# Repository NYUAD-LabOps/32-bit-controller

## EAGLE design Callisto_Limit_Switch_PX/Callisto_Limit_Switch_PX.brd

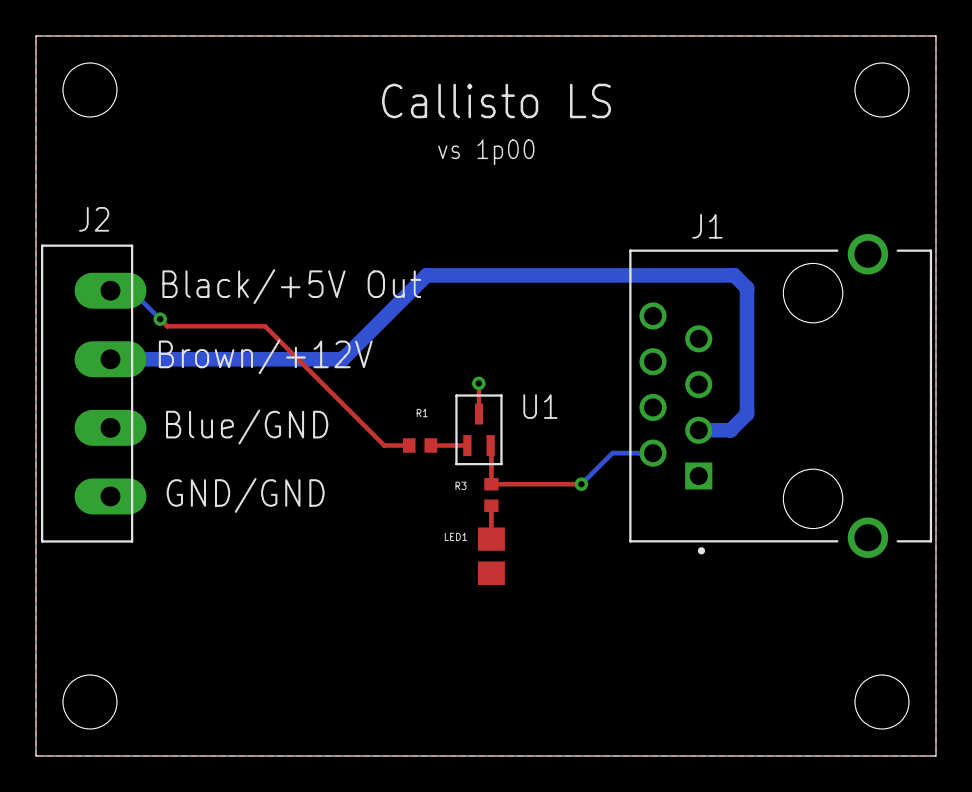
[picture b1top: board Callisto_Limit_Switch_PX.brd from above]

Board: 2 copper layers, 50.0 x 40.0 mm, 6 parts (0 on the bottom side), 6 nets.

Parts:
J1: RJ45_TH_VERT; ASSMANN_A-2014-2S-4-N-R
J2: 4-pos; 1X4_3.81MM_PITCH
LED1: Green; 0805
R1: 2.2K; 0402
R3: 470R0; 0402
U1: NPN; SOT323

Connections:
1_LS: J1.2, R3.P$2, U1.2
BLACK: J2.P$1, R1.P$1
GND: J1.1, J1.6, J2.P$3, J2.P$4, LED1.2
unnamed: R1.P$2, U1.1
unnamed: LED1.1, R3.P$1
VDD12: J1.3, J2.P$2

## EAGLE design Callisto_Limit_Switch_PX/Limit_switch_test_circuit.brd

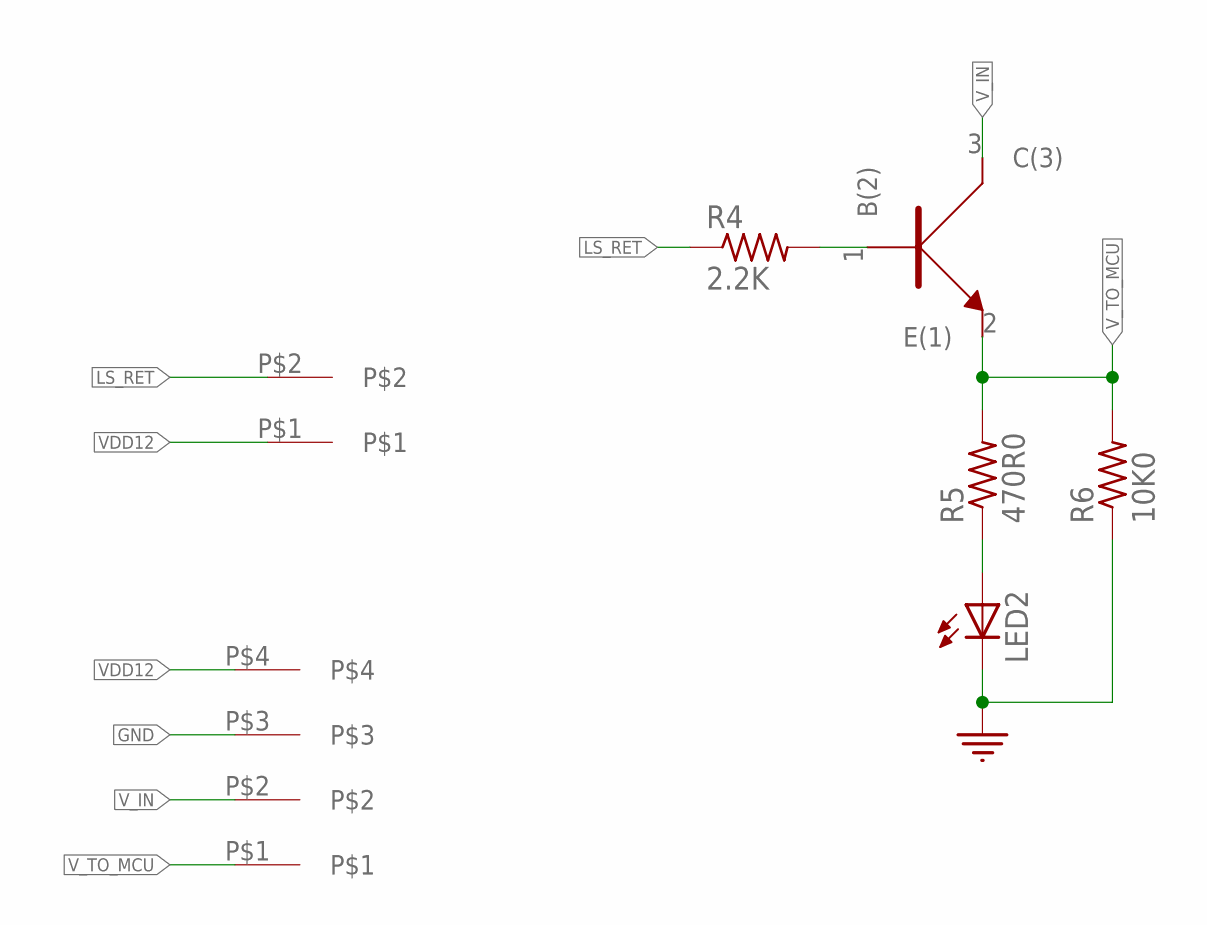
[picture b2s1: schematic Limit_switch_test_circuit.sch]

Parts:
J1: 2-pos; 2_3.81MM_PITCH
J2: 4-pos; 1X4_3.81MM_PITCH
LED2: Green; 0805
R4: 2.2K; 0402
R5: 470R0; 0402
R6: 10K0; 0402
U2: NPN; SOT323

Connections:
GND: J2.P$3, LED2.2 (C), R6.P$1 (1)
LS_RET: J1.P$2, R4.P$1 (1)
unnamed: R4.P$2 (2), U2.1 (B(2))
unnamed: LED2.1 (A), R5.P$1 (1)
VDD12: J1.P$1, J2.P$4
V_IN: J2.P$2, U2.3 (C(3))
V_TO_MCU: J2.P$1, R5.P$2 (2), R6.P$2 (2), U2.2 (E(1))

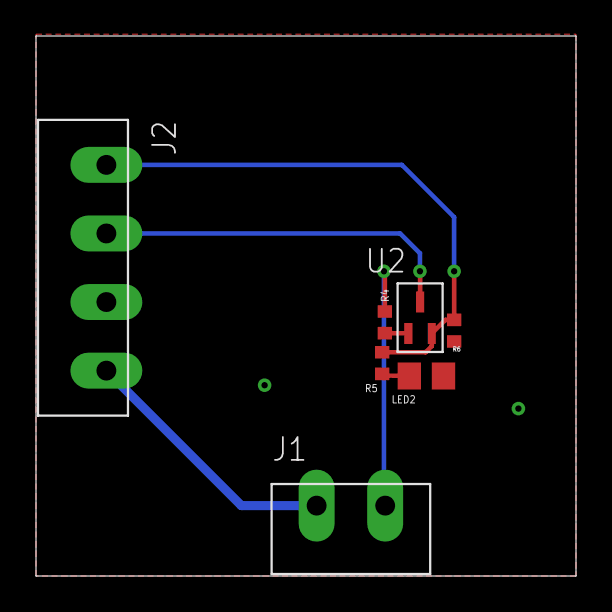
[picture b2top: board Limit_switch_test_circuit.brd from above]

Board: 2 copper layers, 30.0 x 30.0 mm, 7 parts (0 on the bottom side), 7 nets.

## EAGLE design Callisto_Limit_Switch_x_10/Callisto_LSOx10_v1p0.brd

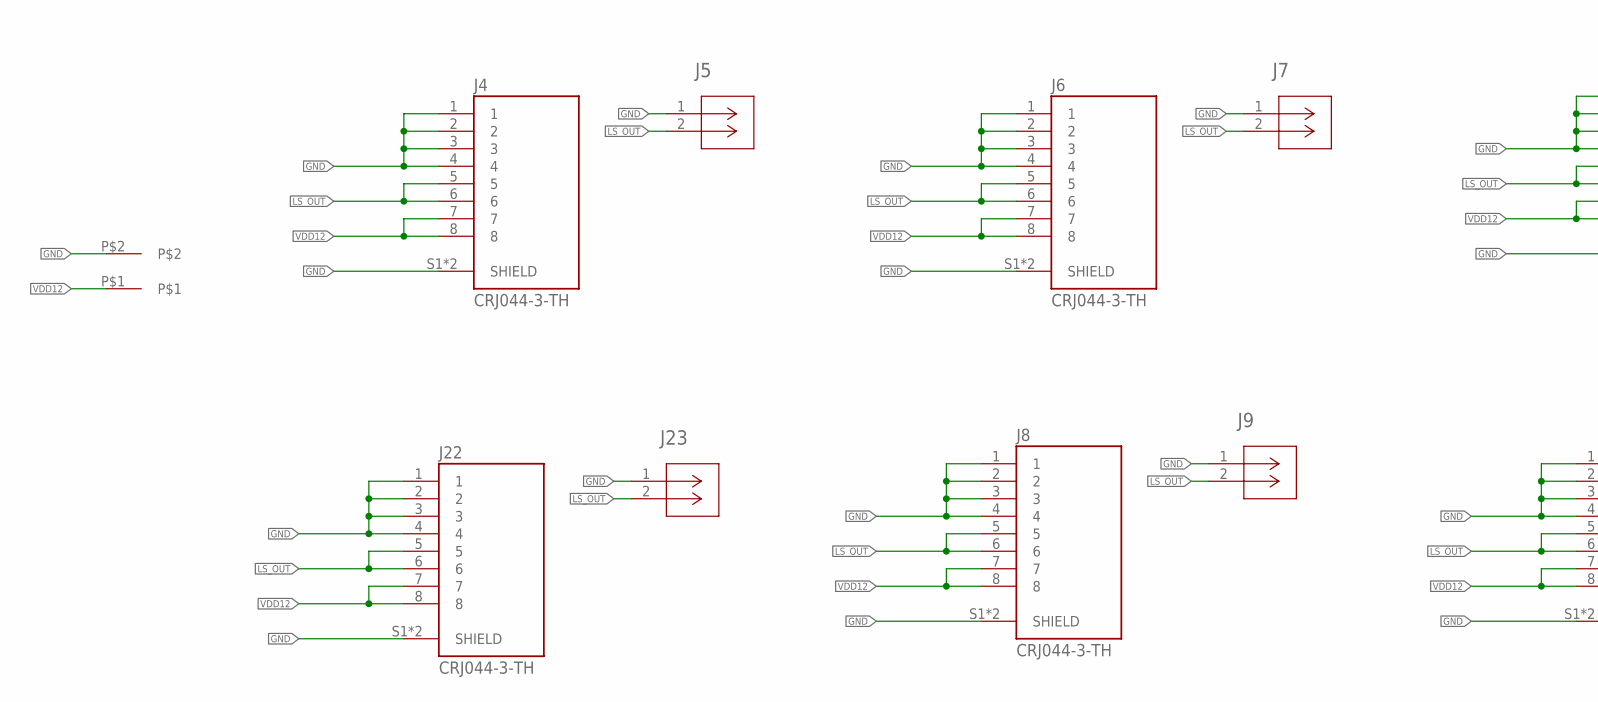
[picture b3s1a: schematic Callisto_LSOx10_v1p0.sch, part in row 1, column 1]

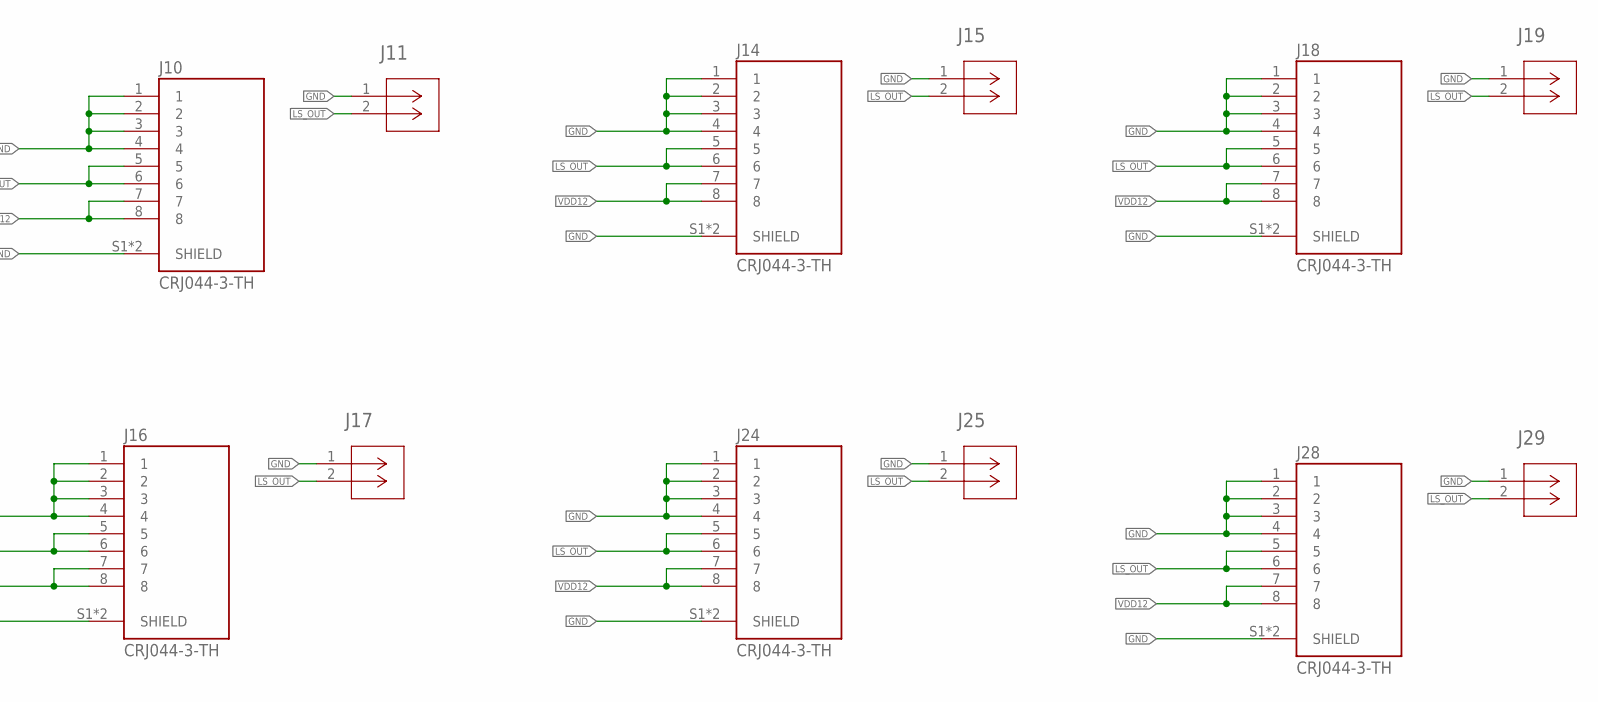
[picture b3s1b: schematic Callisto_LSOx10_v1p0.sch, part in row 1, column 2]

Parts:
J1: 2-pos; 2_3.81MM_PITCH
J4, J6, J8, J10, J14, J16, J18, J22, J24, J28: CRJ044-3-TH; CUI_CRJ044-3-TH
J5, J7, J9, J11, J15, J17, J19, J23, J25, J29: CONN_530470210_PICOBLADE_X_2; CON_530470210_MOL

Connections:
GND: J1.P$2, J4.1, J4.2, J4.3, J4.4, J4.S1 (SHIELD), J4.S2 (SHIELD), J5.1, J6.1, J6.2, J6.3, J6.4, J6.S1 (SHIELD), J6.S2 (SHIELD), J7.1, J8.1, J8.2, J8.3, J8.4, J8.S1 (SHIELD), J8.S2 (SHIELD), J9.1, J10.1, J10.2, J10.3, J10.4, J10.S1 (SHIELD), J10.S2 (SHIELD), J11.1, J14.1, J14.2, J14.3, J14.4, J14.S1 (SHIELD), J14.S2 (SHIELD), J15.1, J16.1, J16.2, J16.3, J16.4, J16.S1 (SHIELD), J16.S2 (SHIELD), J17.1, J18.1, J18.2, J18.3, J18.4, J18.S1 (SHIELD), J18.S2 (SHIELD), J19.1, J22.1, J22.2, J22.3, J22.4, J22.S1 (SHIELD), J22.S2 (SHIELD), J23.1, J24.1, J24.2, J24.3, J24.4, J24.S1 (SHIELD), J24.S2 (SHIELD), J25.1, J28.1, J28.2, J28.3, J28.4, J28.S1 (SHIELD), J28.S2 (SHIELD), J29.1
LS_OUT: J4.5, J4.6, J5.2, J6.5, J6.6, J7.2, J8.5, J8.6, J9.2, J10.5, J10.6, J11.2, J14.5, J14.6, J15.2, J16.5, J16.6, J17.2, J18.5, J18.6, J19.2, J22.5, J22.6, J23.2, J24.5, J24.6, J25.2, J28.5, J28.6, J29.2
VDD12: J1.P$1, J4.7, J4.8, J6.7, J6.8, J8.7, J8.8, J10.7, J10.8, J14.7, J14.8, J16.7, J16.8, J18.7, J18.8, J22.7, J22.8, J24.7, J24.8, J28.7, J28.8

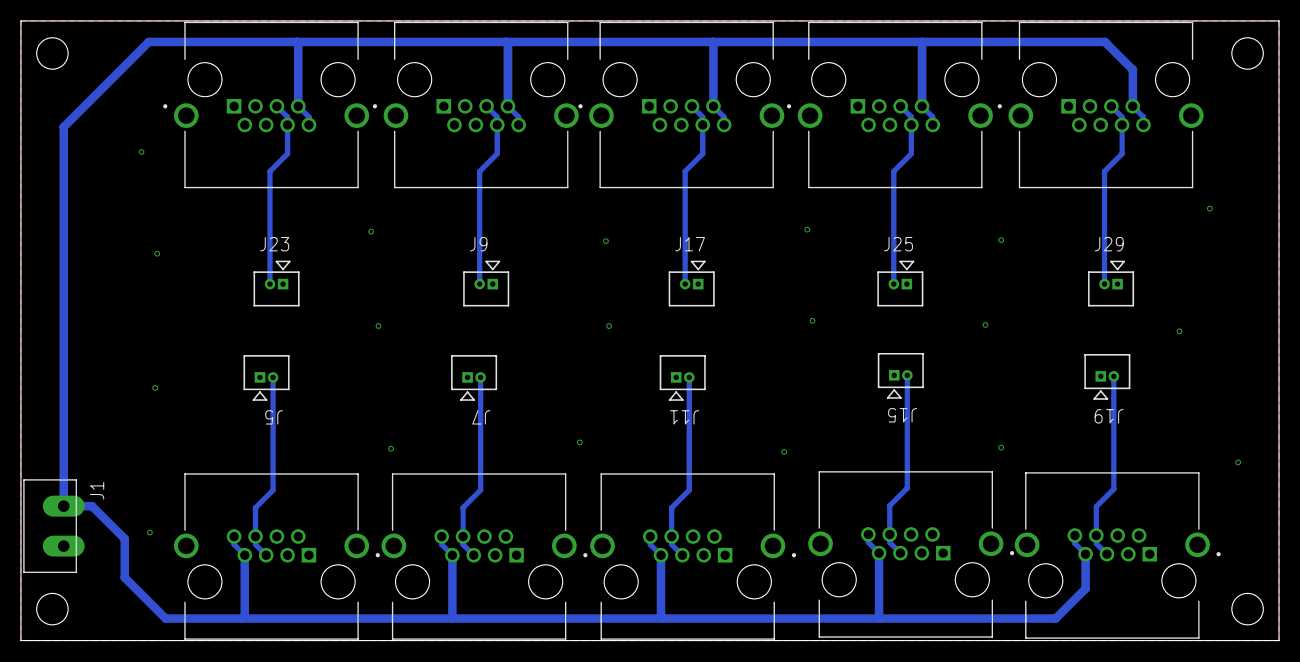
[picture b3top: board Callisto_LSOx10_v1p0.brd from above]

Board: 2 copper layers, 120.0 x 59.1 mm, 21 parts (0 on the bottom side), 3 nets.

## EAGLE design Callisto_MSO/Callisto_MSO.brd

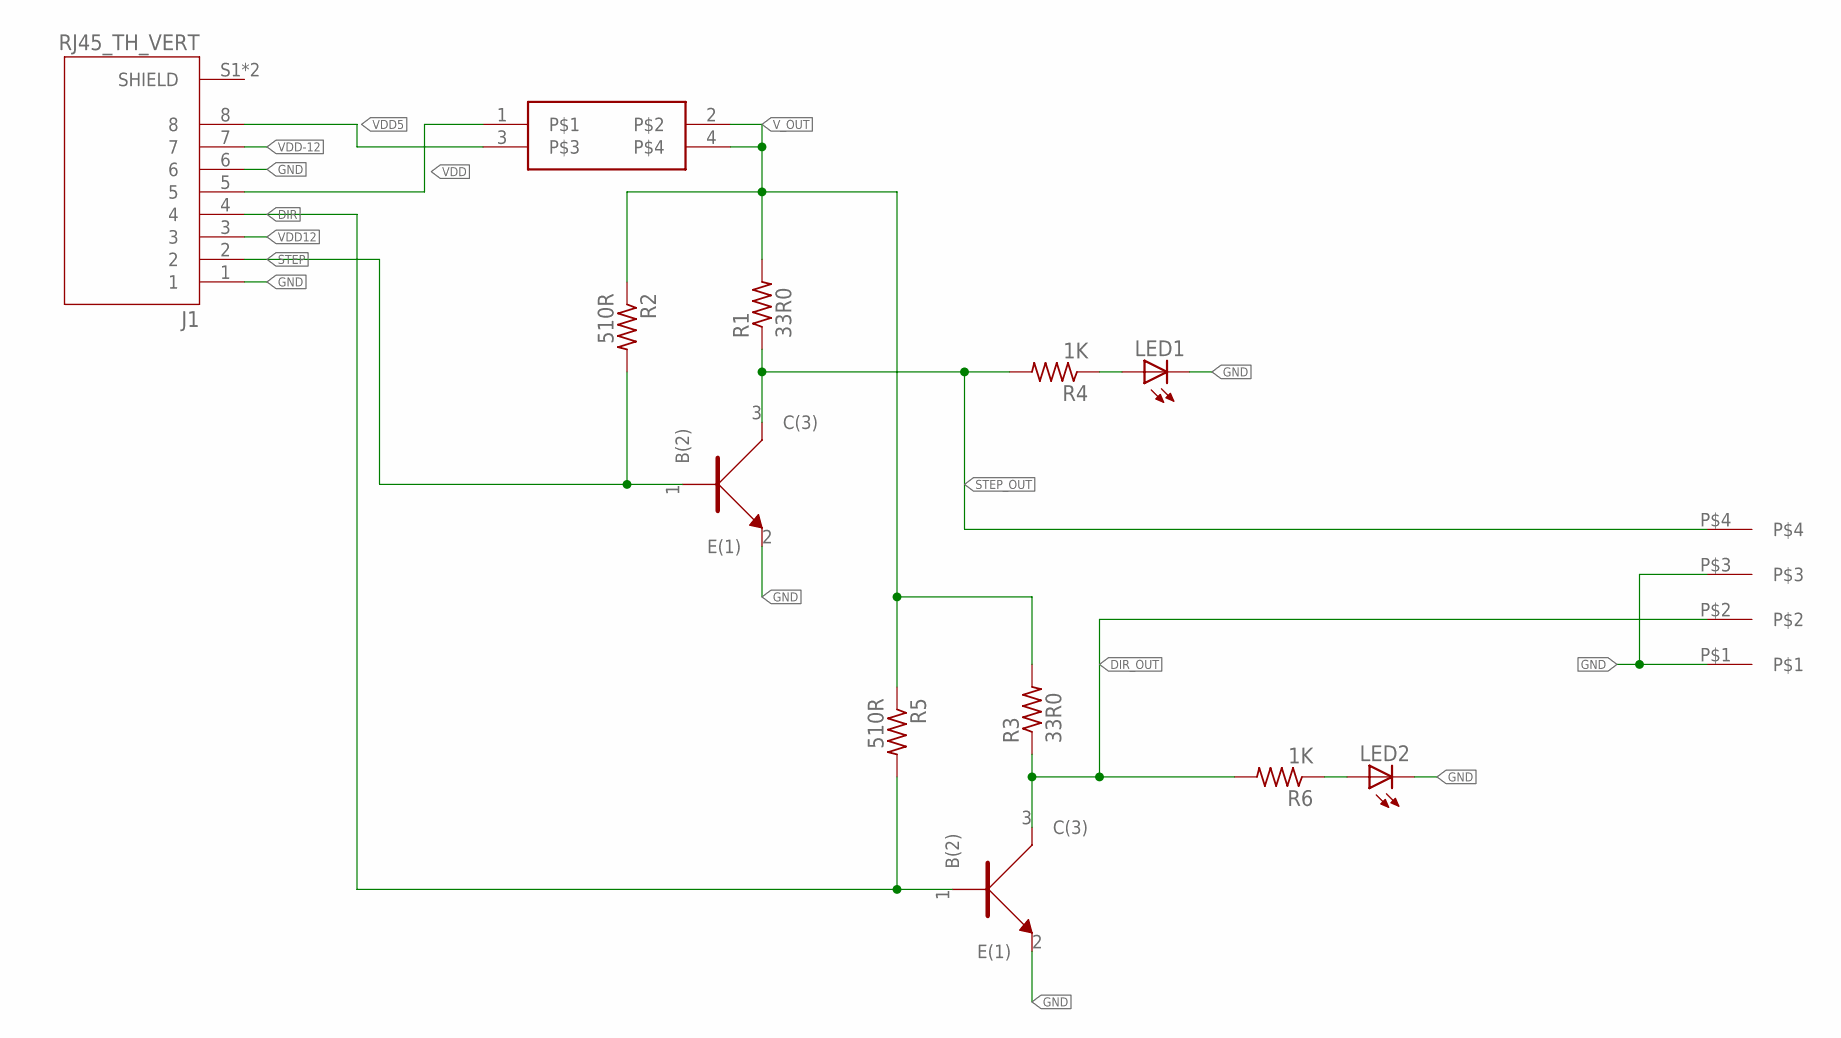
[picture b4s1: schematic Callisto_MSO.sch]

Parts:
J1: RJ45_TH_VERT; ASSMANN_A-2014-2S-4-N-R
J2: 2.54MM_2_X_2_HEADER_GENERIC; 2X2
J3: 4-pos; 1X4_3.81MM_PITCH
LED1, LED2: Green; 0805
R1, R3: 33R0; 0402
R2, R5: 510R; 0402
R4, R6: 1K; 0402
U1, U2: NPN; SOT323

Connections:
DIR: J1.4, R5.P$2 (2), U2.1 (B(2))
DIR_OUT: J3.P$2, R3.P$1 (1), R6.P$2 (2), U2.3 (C(3))
GND: J1.1, J1.6, J3.P$1, J3.P$3, LED1.2 (C), LED2.2 (C), U1.2 (E(1)), U2.2 (E(1))
unnamed: LED2.1 (A), R6.P$1 (1)
unnamed: LED1.1 (A), R4.P$1 (1)
STEP: J1.2, R2.P$2 (2), U1.1 (B(2))
STEP_OUT: J3.P$4, R1.P$1 (1), R4.P$2 (2), U1.3 (C(3))
VDD: J1.5, J2.1
VDD5: J1.8, J2.3
VDD12: J1.3
VDD-12: J1.7
V_OUT: J2.2, J2.4, R1.P$2 (2), R2.P$1 (1), R3.P$2 (2), R5.P$1 (1)

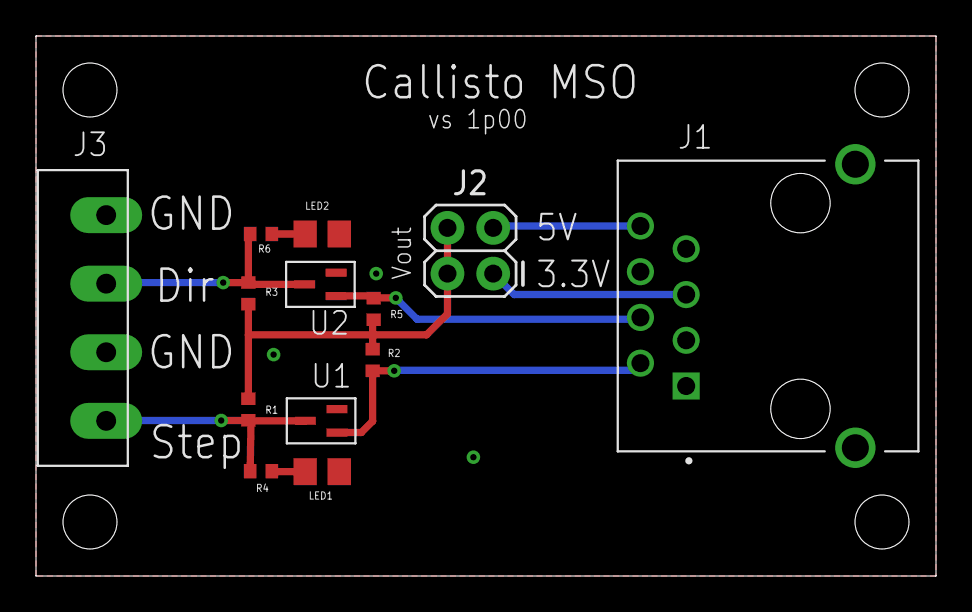
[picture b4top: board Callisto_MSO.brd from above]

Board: 2 copper layers, 50.0 x 30.0 mm, 13 parts (0 on the bottom side), 10 nets.

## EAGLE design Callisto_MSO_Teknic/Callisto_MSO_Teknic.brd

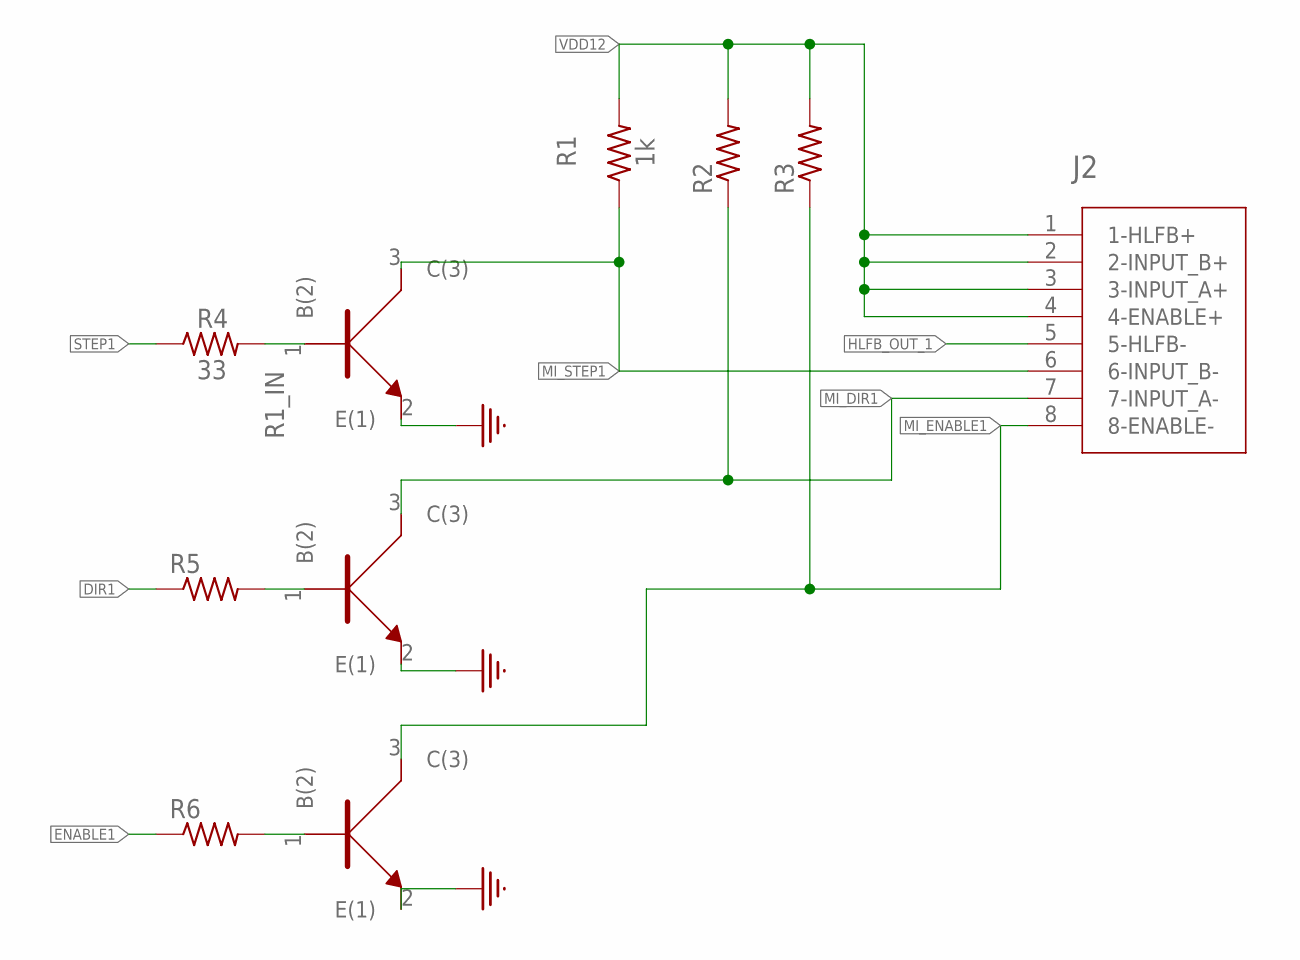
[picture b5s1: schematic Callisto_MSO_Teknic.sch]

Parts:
J2: TEKNIC_8PIN_MOTOR; CON_39281083
R1: 1k; 0805
R2, R3, R5, R6: R_0805; 0805
R4: 33; 0805
U1, U2, U3: NPN; SOT323

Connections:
DIR1: R5.1
ENABLE1: R6.1
GND: U1.2 (E(1)), U2.2 (E(1)), U3.2 (E(1))
HLFB_OUT_1: J2.5 (5-HLFB-)
MI_DIR1: J2.7 (7-INPUT_A-), R2.1, U2.3 (C(3))
MI_ENABLE1: J2.8 (8-ENABLE-), R3.1, U3.3 (C(3))
MI_STEP1: J2.6 (6-INPUT_B-), R1.1, U1.3 (C(3))
unnamed: R5.2, U2.1 (B(2))
unnamed: R6.2, U3.1 (B(2))
R1_IN: R4.2, U1.1 (B(2))
STEP1: R4.1
VDD12: J2.1 (1-HLFB+), J2.2 (2-INPUT_B+), J2.3 (3-INPUT_A+), J2.4 (4-ENABLE+), R1.2, R2.2, R3.2

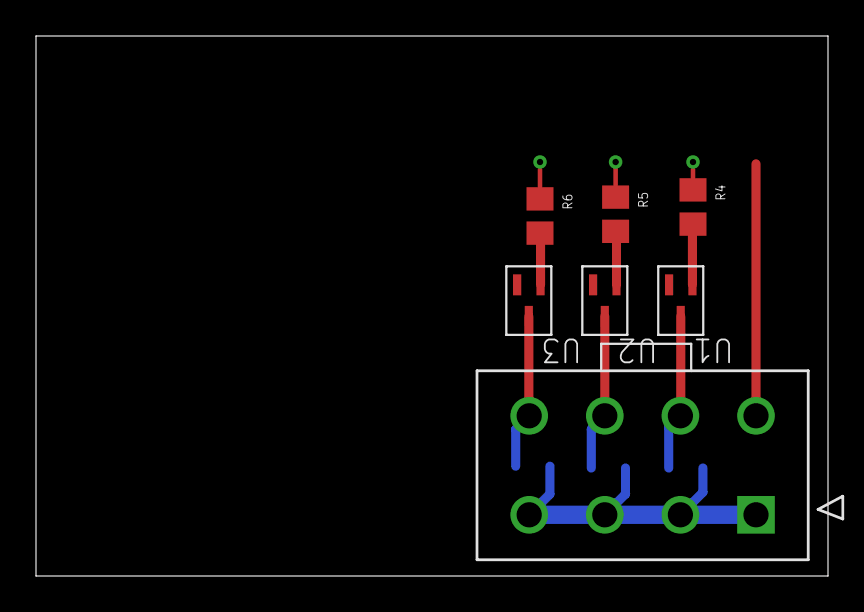
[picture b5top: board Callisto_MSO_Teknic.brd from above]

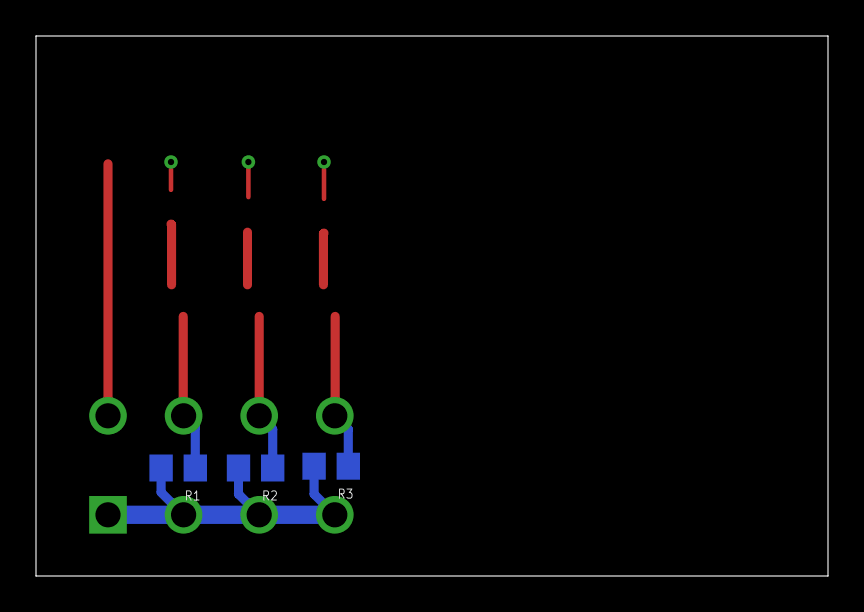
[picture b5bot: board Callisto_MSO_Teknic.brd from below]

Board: 2 copper layers, 44.0 x 30.0 mm, 10 parts (3 on the bottom side), 8 nets.

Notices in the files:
parts and their libraries:
COPYRIGHT: Copyright (C) 2022 Ultra Librarian. All rights reserved.
